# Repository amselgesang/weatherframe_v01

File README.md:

# weatherframe_v01
My weather station hardver

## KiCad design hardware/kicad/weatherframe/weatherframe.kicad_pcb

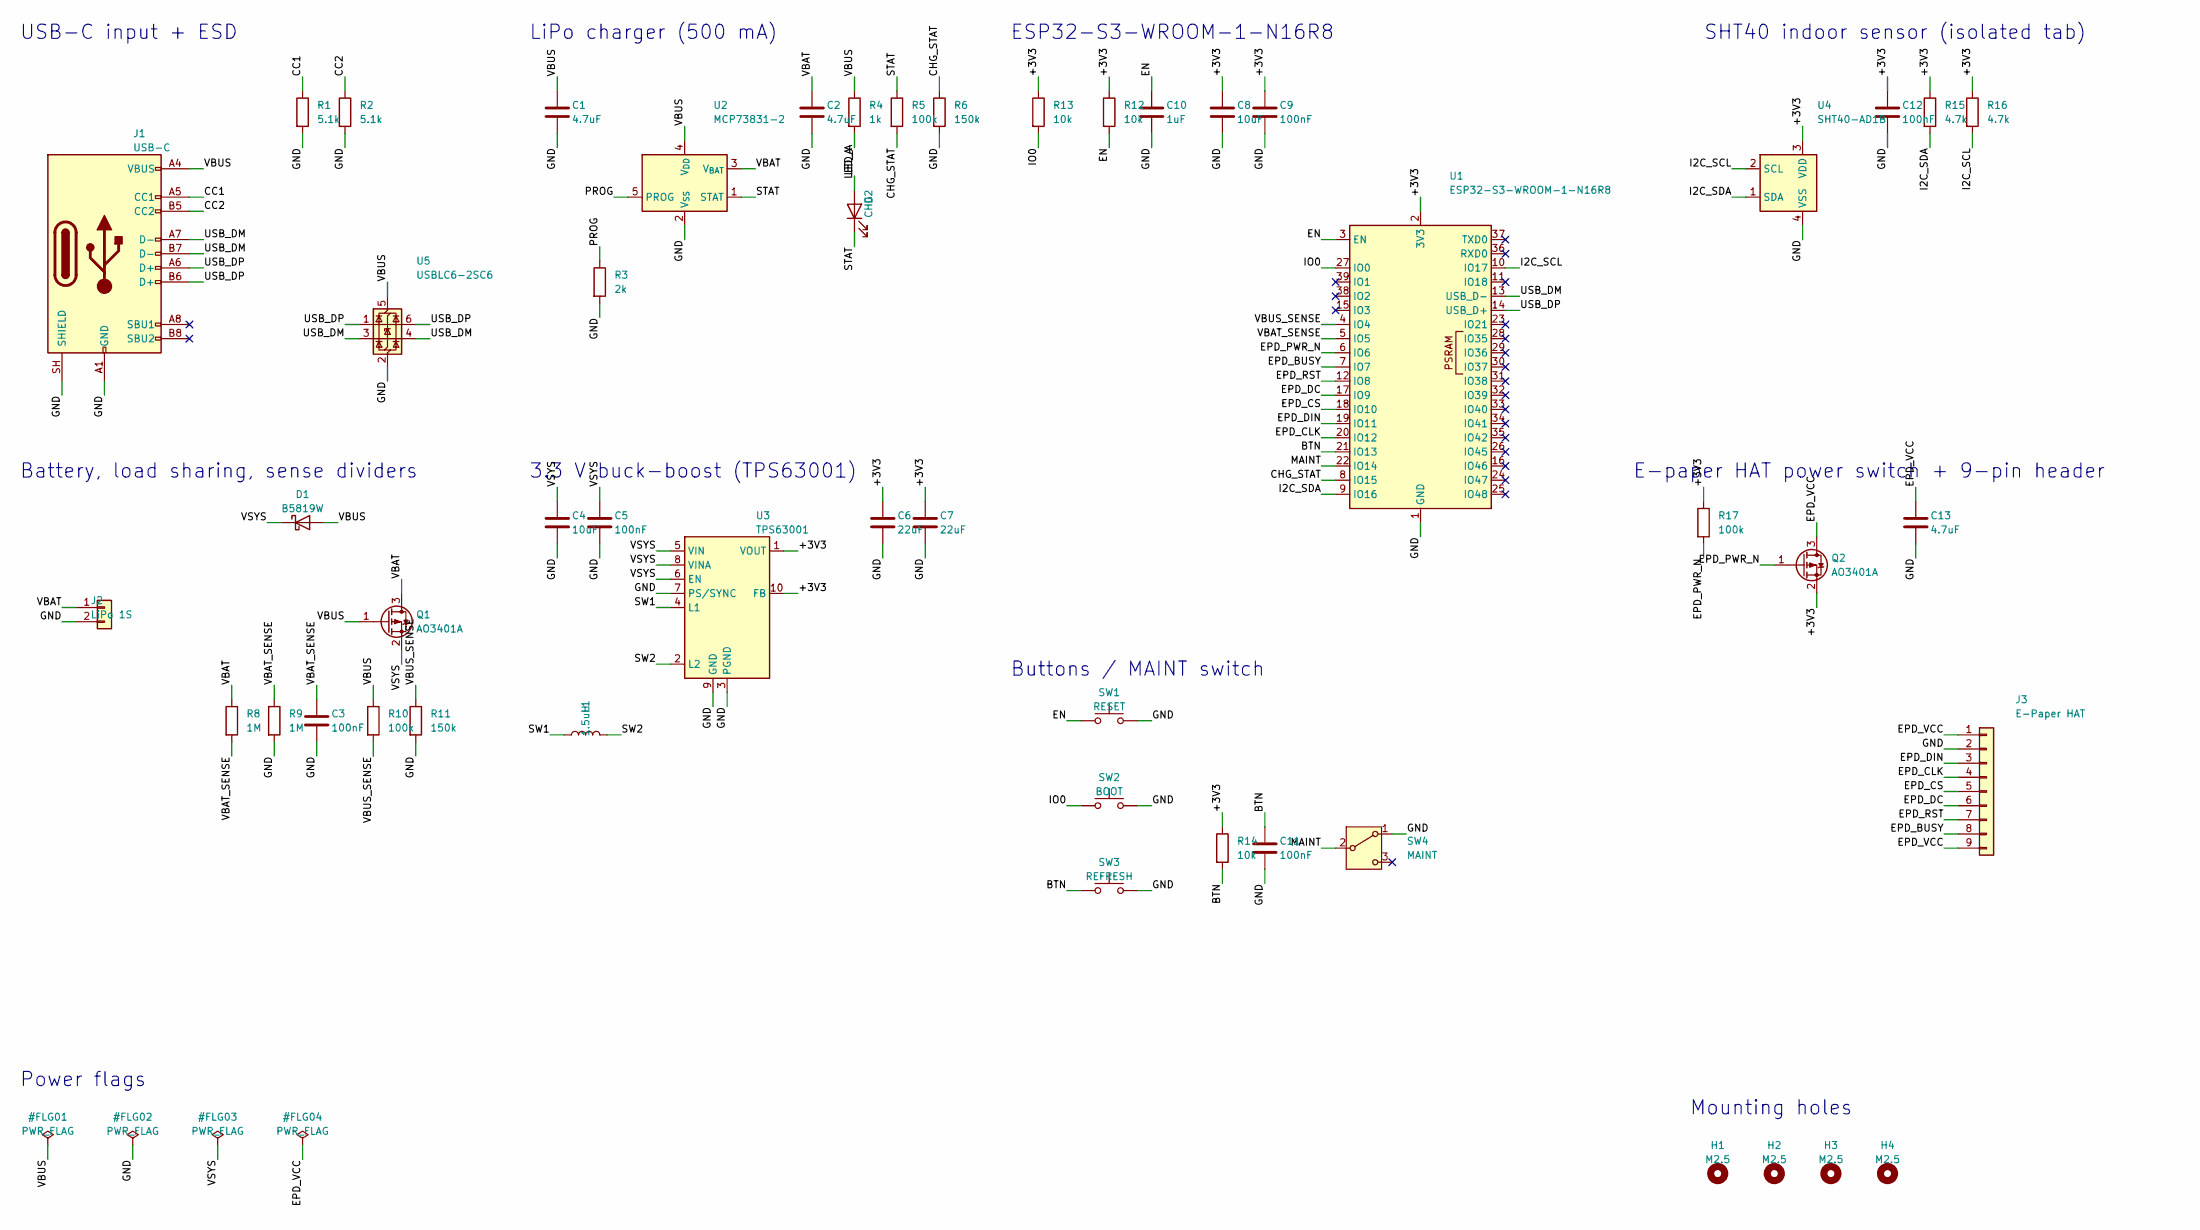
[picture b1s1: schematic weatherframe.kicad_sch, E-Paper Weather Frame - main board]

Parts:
C1, C2, C13: 4.7uF; C_0603_1608Metric; MPN 4.7uF; LCSC C19666
C3, C5, C9, C11, C12: 100nF; C_0402_1005Metric; MPN 100nF; LCSC C1525
C4: 10uF; C_0805_2012Metric; MPN 10uF; LCSC C15850
C6, C7: 22uF; C_0805_2012Metric; MPN 22uF; LCSC C45783
C8: 10uF; C_0603_1608Metric; MPN 10uF; LCSC C19702
C10: 1uF; C_0402_1005Metric; MPN 1uF; LCSC C52923
D1: B5819W; D_SOD-123; MPN B5819W; LCSC C8598
D2: CHG; LED_0603_1608Metric; MPN KT-0603R; LCSC C2286
H1, H2, H3, H4: M2.5; MountingHole_2.7mm_M2.5; MPN M2.5
J1: USB-C; USB_C_Receptacle_HRO_TYPE-C-31-M-12; MPN TYPE-C-31-M-12; LCSC C165948
J2: LiPo 1S; JST_PH_S2B-PH-SM4-TB_1x02-1MP_P2.00mm_Horizontal; MPN PH-2AWT (JST PH 2.0); LCSC C2763693
J3: E-Paper HAT; PinHeader_1x09_P2.54mm_Vertical; MPN 1x9 pin header 2.54 mm (hand-solder)
L1: 1.5uH; L_Changjiang_FNR4030S; MPN SWPA4030S1R5NT; LCSC C42100
Q1, Q2: AO3401A; SOT-23; MPN AO3401A; LCSC C15127
R1, R2: 5.1k; R_0402_1005Metric; MPN 5.1k; LCSC C25905
R3: 2k; R_0402_1005Metric; MPN 2k; LCSC C4109
R4: 1k; R_0402_1005Metric; MPN 1k; LCSC C11702
R5, R10, R17: 100k; R_0402_1005Metric; MPN 100k; LCSC C25741
R6, R11: 150k; R_0402_1005Metric; MPN 100k; LCSC C25755
R8, R9: 1M; R_0402_1005Metric; MPN 1M; LCSC C26083
R12, R13, R14: 10k; R_0402_1005Metric; MPN 10k; LCSC C25744
R15, R16: 4.7k; R_0402_1005Metric; MPN 4.7k; LCSC C25900
SW1: RESET; SW_Push_1P1T_XKB_TS-1187A; MPN TS-1187A-B-A-B; LCSC C318884
SW2: BOOT; SW_Push_1P1T_XKB_TS-1187A; MPN TS-1187A-B-A-B; LCSC C318884
SW3: REFRESH; SW_Push_1P1T_XKB_TS-1187A; MPN TS-1187A-B-A-B; LCSC C318884
SW4: MAINT; SW_SPDT_Shouhan_MSK12C02; MPN MSK12C02; LCSC C431540
U1: ESP32-S3-WROOM-1-N16R8; ESP32-S3-WROOM-1; MPN ESP32-S3-WROOM-1-N16R8; LCSC C2913202
U2: MCP73831-2; SOT-23-5; MPN MCP73831T-2ACI/OT; LCSC C424093
U3: TPS63001; Texas_DRC0010J; MPN TPS63001DRCR; LCSC C28060
U4: SHT40-AD1B; Sensirion_DFN-4_1.5x1.5mm_P0.8mm_SHT4x_NoCentralPad; MPN SHT40-AD1B-R2; LCSC C2909890
U5: USBLC6-2SC6; SOT-23-6; MPN USBLC6-2SC6; LCSC C7519

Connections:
+3V3: C6.1, C7.1, C8.1, C9.1, C12.1, Q2.2 (S), R12.1, R13.1, R14.1, R15.1, R16.1, R17.1, U1.2 (3V3), U3.1 (VOUT), U3.10 (FB), U4.3 (VDD)
BTN: C11.1, R14.2, SW3.1, U1.21 (IO13)
CC1: J1.A5 (CC1), R1.1
CC2: J1.B5 (CC2), R2.1
CHG_STAT: R5.2, R6.1, U1.8 (IO15)
EN: C10.1, R12.2, SW1.1, U1.3 (EN)
EPD_BUSY: J3.8, U1.7 (IO7)
EPD_CLK: J3.4, U1.20 (IO12)
EPD_CS: J3.5, U1.18 (IO10)
EPD_DC: J3.6, U1.17 (IO9)
EPD_DIN: J3.3, U1.19 (IO11)
EPD_PWR_N: Q2.1 (G), R17.2, U1.6 (IO6)
EPD_RST: J3.7, U1.12 (IO8)
EPD_VCC: C13.1, J3.1, J3.9, Q2.3 (D)
GND: C1.2, C2.2, C3.2, C4.2, C5.2, C6.2, C7.2, C8.2, C9.2, C10.2, C11.2, C12.2, C13.2, J1.A1 (GND), J1.A12 (GND), J1.B1 (GND), J1.B12 (GND), J1.SH (SHIELD), J2.2, J3.2, R1.2, R2.2, R3.2, R6.2, R9.2, R11.2, SW1.2, SW2.2, SW3.2, SW4.1 (A), SW4.SH, U1.1 (GND), U1.40 (GND), U1.41 (GND), U2.2 (V_{SS}), U3.3 (PGND), U3.7 (PS/SYNC), U3.9 (GND), U3.11 (PGND), U4.4 (VSS), U5.2 (GND)
I2C_SCL: R16.2, U1.10 (IO17), U4.2 (SCL)
I2C_SDA: R15.2, U1.9 (IO16), U4.1 (SDA)
IO0: R13.2, SW2.1, U1.27 (IO0)
LED_A: D2.2 (A), R4.2
MAINT: SW4.2 (B), U1.22 (IO14)
PROG: R3.1, U2.5 (PROG)
STAT: D2.1 (K), R5.1, U2.1 (STAT)
SW1: L1.1, U3.4 (L1)
SW2: L1.2, U3.2 (L2)
USB_DM: J1.A7 (D-), J1.B7 (D-), U1.13 (USB_D-), U5.3 (I/O2), U5.4 (I/O2)
USB_DP: J1.A6 (D+), J1.B6 (D+), U1.14 (USB_D+), U5.1 (I/O1), U5.6 (I/O1)
VBAT: C2.1, J2.1, Q1.3 (D), R8.1, U2.3 (V_{BAT})
VBAT_SENSE: C3.1, R8.2, R9.1, U1.5 (IO5)
VBUS: C1.1, D1.2 (A), J1.A4 (VBUS), J1.A9 (VBUS), J1.B4 (VBUS), J1.B9 (VBUS), Q1.1 (G), R4.1, R10.1, U2.4 (V_{DD}), U5.5 (VBUS)
VBUS_SENSE: R10.2, R11.1, U1.4 (IO4)
VSYS: C4.1, C5.1, D1.1 (K), Q1.2 (S), U3.5 (VIN), U3.6 (EN), U3.8 (VINA)

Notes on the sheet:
USB-C input + ESD
LiPo charger (500 mA)
Battery, load sharing, sense dividers
3.3 V buck-boost (TPS63001)
ESP32-S3-WROOM-1-N16R8
Buttons / MAINT switch
SHT40 indoor sensor (isolated tab)
E-paper HAT power switch + 9-pin header
Mounting holes
Power flags

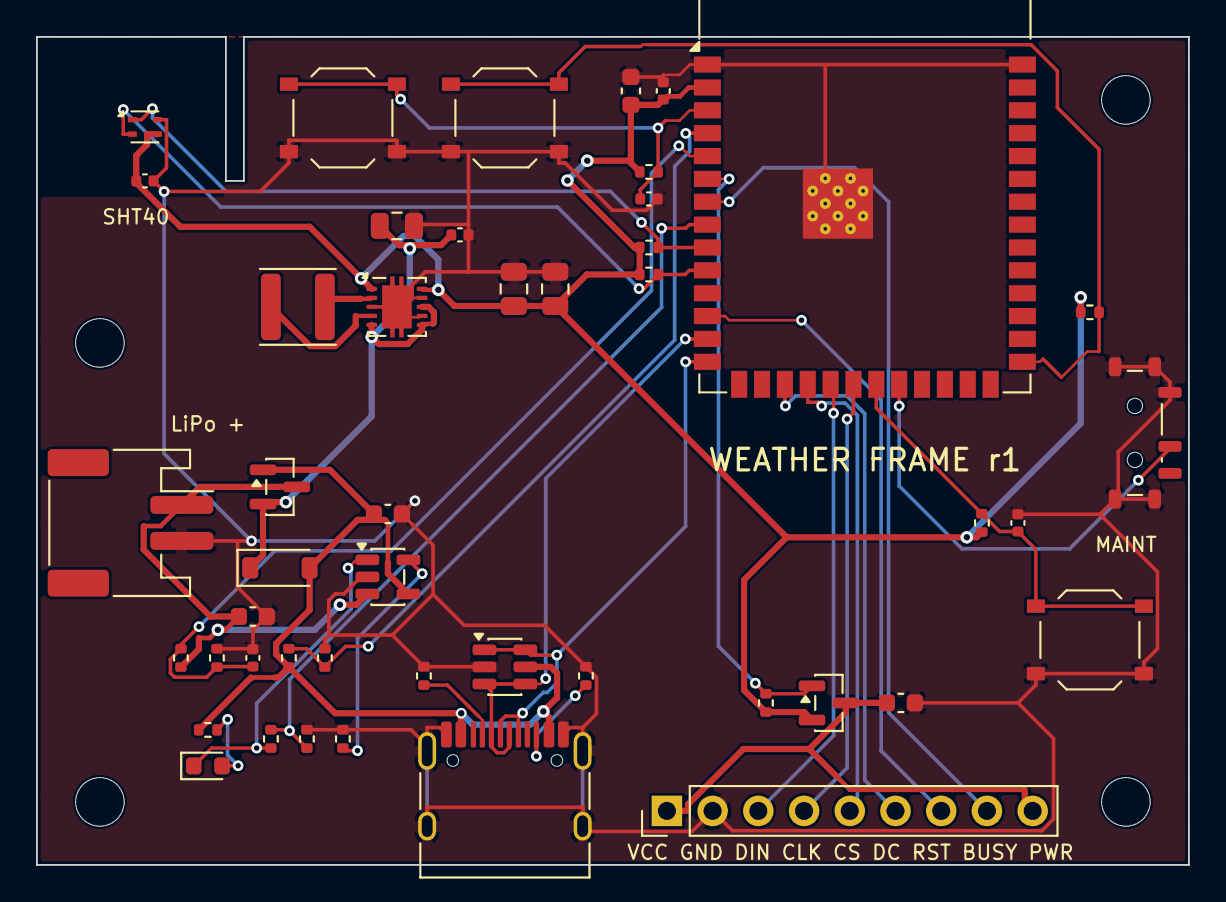
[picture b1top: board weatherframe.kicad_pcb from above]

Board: 2 copper layers, 64.0 x 46.0 mm, 50 parts (0 on the bottom side), 31 nets.

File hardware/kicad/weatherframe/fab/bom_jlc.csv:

Comment,Designator,Footprint,LCSC Part #
USB-C,J1,USB_C_Receptacle_HRO_TYPE-C-31-M-12,C165948
5.1k,"R1,R2",R_0402_1005Metric,C25905
USBLC6-2SC6,U5,SOT-23-6,C7519
MCP73831-2,U2,SOT-23-5,C424093
4.7uF,"C1,C2,C13",C_0603_1608Metric,C19666
2k,R3,R_0402_1005Metric,C4109
1k,R4,R_0402_1005Metric,C11702
CHG,D2,LED_0603_1608Metric,C2286
100k,"R5,R10,R17",R_0402_1005Metric,C25741
150k,"R6,R11",R_0402_1005Metric,C25755
LiPo 1S,J2,JST_PH_S2B-PH-SM4-TB_1x02-1MP_P2.00mm_Horizontal,C2763693
B5819W,D1,D_SOD-123,C8598
AO3401A,"Q1,Q2",SOT-23,C15127
1M,"R8,R9",R_0402_1005Metric,C26083
100nF,"C3,C5,C9,C11,C12",C_0402_1005Metric,C1525
TPS63001,U3,Texas_DRC0010J,C28060
1.5uH,L1,L_Changjiang_FNR4030S,C42100
10uF,C4,C_0805_2012Metric,C15850
22uF,"C6,C7",C_0805_2012Metric,C45783
ESP32-S3-WROOM-1-N16R8,U1,ESP32-S3-WROOM-1,C2913202
10uF,C8,C_0603_1608Metric,C19702
10k,"R12,R13,R14",R_0402_1005Metric,C25744
1uF,C10,C_0402_1005Metric,C52923
RESET,SW1,SW_Push_1P1T_XKB_TS-1187A,C318884
BOOT,SW2,SW_Push_1P1T_XKB_TS-1187A,C318884
REFRESH,SW3,SW_Push_1P1T_XKB_TS-1187A,C318884
MAINT,SW4,SW_SPDT_Shouhan_MSK12C02,C431540
SHT40-AD1B,U4,Sensirion_DFN-4_1.5x1.5mm_P0.8mm_SHT4x_NoCentralPad,C2909890
4.7k,"R15,R16",R_0402_1005Metric,C25900

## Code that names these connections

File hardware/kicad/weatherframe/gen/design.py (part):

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    R("R2", "5.1k", "CC2", "GND", (83.82, 50.8), pcb=(30.5, 35.5, 90, "F")),
    dict(ref="U5", sym="Power_Protection:USBLC6-2SC6", fp="Package_TO_SOT_SMD:SOT-23-6",
         value="USBLC6-2SC6", lcsc="C7519", mpn="USBLC6-2SC6",
         pins={"1": "USB_DP", "6": "USB_DP", "3": "USB_DM", "4": "USB_DM", "2": "GND", "5": "VBUS"},
         pos=(91.44, 88.9), pcb=(26, 35.0, 0, "F")),

    # ---------------- Charger ----------------
    dict(ref="U2", sym="Battery_Management:MCP73831-2-OT", fp="Package_TO_SOT_SMD:SOT-23-5",
         value="MCP73831-2", lcsc="C424093", mpn="MCP73831T-2ACI/OT",
         pins={"4": "VBUS", "2": "GND", "3": "VBAT", "5": "PROG", "1": "STAT"},
         pos=(144.78, 63.5), pcb=(19.5, 30, 0, "F")),
    C("C1", "4.7uF", "VBUS", "GND", (121.92, 50.8), fp=C0603, pcb=(19.5, 26.5, 0, "F")),
    C("C2", "4.7uF", "VBAT", "GND", (167.64, 50.8), fp=C0603, pcb=(12, 32.2, 0, "F")),
    R("R3", "2k", "PROG", "GND", (129.54, 81.28), pcb=(17, 39, 90, "F")),           # 500 mA charge current
    R("R4", "1k", "VBUS", "LED_A", (175.26, 50.8), pcb=(9.5, 38.5, 0, "F")),
    dict(ref="D2", sym="Device:LED", fp="LED_SMD:LED_0603_1608Metric", value="CHG", lcsc="C2286", mpn="KT-0603R",
         pins={"2": "LED_A", "1": "STAT"}, pos=(175.26, 68.58), rot=90, pcb=(9.5, 40.5, 0, "F")),
    R("R5", "100k", "STAT", "CHG_STAT", (182.88, 50.8), pcb=(13, 39, 90, "F")),
    R("R6", "150k", "CHG_STAT", "GND", (190.5, 50.8), pcb=(15, 39, 90, "F")),      # 100k/150k: 5 V -> 3.0 V (ESP32-S3 VIH min = 2.475 V)

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         value="LiPo 1S", lcsc="C2763693", mpn="PH-2AWT (JST PH 2.0)",
         pins={"1": "VBAT", "2": "GND"}, pos=(40.64, 139.7), pcb=(5.2, 27, -90, "F")),
    dict(ref="D1", sym="Device:D_Schottky", fp="Diode_SMD:D_SOD-123", value="B5819W", lcsc="C8598", mpn="B5819W",
         pins={"2": "VBUS", "1": "VSYS"}, pos=(76.2, 124.46), pcb=(13.5, 29.5, 0, "F")),
    dict(ref="Q1", sym="Transistor_FET:AO3401A", fp="Package_TO_SOT_SMD:SOT-23", value="AO3401A", lcsc="C15127", mpn="AO3401A",
         pins={"1": "VBUS", "2": "VSYS", "3": "VBAT"}, pos=(91.44, 142.24), pcb=(13.5, 25, 0, "F")),
    R("R8", "1M", "VBAT", "VBAT_SENSE", (63.5, 160.02), pcb=(8, 34.5, 90, "F")),
    R("R9", "1M", "VBAT_SENSE", "GND", (71.12, 160.02), pcb=(10, 34.5, 90, "F")),
    C("C3", "100nF", "VBAT_SENSE", "GND", (78.74, 160.02), pcb=(12, 34.5, 90, "F")),
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    # ---------------- 3.3 V buck-boost ----------------
    dict(ref="U3", sym="Regulator_Switching:TPS63001", fp="Package_SON:Texas_DRC0010J",
         value="TPS63001", lcsc="C28060", mpn="TPS63001DRCR",
         pins={"5": "VSYS", "8": "VSYS", "6": "VSYS", "7": "GND", "3": "GND", "11": "GND", "9": "GND",
               "4": "SW1", "2": "SW2", "1": "+3V3", "10": "+3V3"},
         pos=(152.4, 139.7), pcb=(20, 15, 0, "F")),
    dict(ref="L1", sym="Device:L", fp="Inductor_SMD:L_Changjiang_FNR4030S", value="1.5uH", lcsc="C42100",
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    dict(ref="SW2", sym="Switch:SW_Push", fp="Button_Switch_SMD:SW_Push_1P1T_XKB_TS-1187A", value="BOOT",
         lcsc="C318884", mpn="TS-1187A-B-A-B", pins={"1": "IO0", "2": "GND"}, pos=(220.98, 175.26), pcb=(26, 4.5, 0, "F")),
    dict(ref="SW3", sym="Switch:SW_Push", fp="Button_Switch_SMD:SW_Push_1P1T_XKB_TS-1187A", value="REFRESH",
         lcsc="C318884", mpn="TS-1187A-B-A-B", pins={"1": "BTN", "2": "GND"}, pos=(220.98, 190.5), pcb=(58.5, 33.5, 0, "F")),
    R("R14", "10k", "+3V3", "BTN", (241.3, 182.88), pcb=(52.5, 27, 90, "F")),
    C("C11", "100nF", "BTN", "GND", (248.92, 182.88), pcb=(54.5, 27, 90, "F")),
    dict(ref="SW4", sym="Switch:SW_SPDT", fp="Button_Switch_SMD:SW_SPDT_Shouhan_MSK12C02", value="MAINT",
         lcsc="C431540", mpn="MSK12C02", pins={"2": "MAINT", "1": "GND", "3": None}, pos=(266.7, 182.88),
         pcb=(61.0, 22, -90, "F")),

    # ---------------- SHT40 (on the isolated corner tab) ----------------
    dict(ref="U4", sym="Sensor_Humidity:SHT4x", fp="Sensor_Humidity:Sensirion_DFN-4_1.5x1.5mm_P0.8mm_SHT4x_NoCentralPad",
         value="SHT40-AD1B", lcsc="C2909890", mpn="SHT40-AD1B-R2",
         pins={"1": "I2C_SDA", "2": "I2C_SCL", "3": "+3V3", "4": "GND"}, pos=(342.9, 63.5), pcb=(6, 5, 0, "F")),
    C("C12", "100nF", "+3V3", "GND", (360.68, 50.8), pcb=(6, 8, 0, "F")),
    R("R15", "4.7k", "+3V3", "I2C_SDA", (368.3, 50.8), pcb=(34, 11.7, 0, "F")),
    R("R16", "4.7k", "+3V3", "I2C_SCL", (375.92, 50.8), pcb=(34, 13.2, 0, "F")),

    # ---------------- E-paper power switch + header ----------------
    dict(ref="Q2", sym="Transistor_FET:AO3401A", fp="Package_TO_SOT_SMD:SOT-23", value="AO3401A", lcsc="C15127", mpn="AO3401A",
         pins={"1": "EPD_PWR_N", "2": "+3V3", "3": "EPD_VCC"}, pos=(345.44, 132.08), pcb=(44, 37, 0, "F")),
    R("R17", "100k", "+3V3", "EPD_PWR_N", (327.66, 124.46), pcb=(40.5, 37, 90, "F")),
    C("C13", "4.7uF", "EPD_VCC", "GND", (365.76, 124.46), fp=C0603, pcb=(48, 37, 0, "F")),
    dict(ref="J3", sym="Connector_Generic:Conn_01x09", fp="Connector_PinHeader_2.54mm:PinHeader_1x09_P2.54mm_Vertical",
         value="E-Paper HAT", lcsc="", mpn="1x9 pin header 2.54 mm (hand-solder)",
         pins={"1": "EPD_VCC", "2": "GND", "3": "EPD_DIN", "4": "EPD_CLK", "5": "EPD_CS", "6": "EPD_DC",
               "7": "EPD_RST", "8": "EPD_BUSY", "9": "EPD_VCC"},
         pos=(378.46, 172.72), pcb=(35, 43, 90, "F"), hand_solder=True),

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
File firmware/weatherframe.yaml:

# E-paper weather frame — device firmware for the custom ESP32-S3 board.
#   esphome run weatherframe.yaml          (first time over USB-C, later OTA in MAINT mode)
#
# Wake cycle (every 15 min, aligned to :00/:15/:30/:45):
#   boot -> read SHT40 + battery -> Wi-Fi -> Open-Meteo -> refresh e-paper -> deep sleep
# MAINT switch ON keeps the board awake for OTA and logs. The button forces a refresh.

substitutions:
  name: weatherframe
  location_name: "Budapest"
  latitude: "47.4979"
  longitude: "19.0402"
  german: "true"          # "false" for English labels
  fahrenheit: "false"     # "true" for °F / mph
  interval_s: "900"       # wake interval in seconds
  quiet_start: "0"        # no updates from 00:00 ...
  quiet_end: "6"          # ... until 06:00 local time (set both equal to disable)
  low_battery_v: "3.40"

  # Pin map (must match hardware/kicad/weatherframe)
  pin_sda: GPIO16
  pin_scl: GPIO17
  pin_vbus: GPIO4
  pin_vbat: GPIO5
  pin_epd_pwr: GPIO6      # low = HAT powered (P-FET gate)
  pin_epd_busy: GPIO7
  pin_epd_rst: GPIO8
  pin_epd_dc: GPIO9
  pin_epd_cs: GPIO10
  pin_epd_mosi: GPIO11
  pin_epd_clk: GPIO12
  pin_button: GPIO13
  pin_maint: GPIO14
  pin_chg: GPIO15

esphome:
  name: ${name}
  friendly_name: Weather Frame
  on_boot:
    priority: -100
    then:
      - script.execute: wake_cycle

esp32:
  variant: esp32s3
  board: esp32-s3-devkitc-1
  flash_size: 16MB
  framework:
    type: esp-idf

psram:
  mode: octal
  speed: 80MHz

packages:
  common: !include weatherframe/common.yaml

logger:
  level: INFO
  hardware_uart: USB_SERIAL_JTAG

wifi:
  ssid: !secret wifi_ssid
  password: !secret wifi_password
  fast_connect: true
  reboot_timeout: 0s
  power_save_mode: light
  # A static IP saves ~1 s of DHCP per wake. Uncomment and adjust:
  # manual_ip:
  #   static_ip: 192.168.1.60
  #   gateway: 192.168.1.1
  #   subnet: 255.255.255.0
  #   dns1: 192.168.1.1

ota:
  - platform: esphome
    password: !secret ota_password

time:
  - platform: sntp
    id: wf_clock

deep_sleep:
  id: sleeper
  sleep_duration: 15min
  run_duration: 90s       # safety net: never stay awake longer than this (unless MAINT)
  wakeup_pin:
    number: ${pin_button}
    inverted: true        # button pulls low; external 10k pull-up on the board
    allow_other_uses: true

i2c:
  sda: ${pin_sda}
  scl: ${pin_scl}
  frequency: 400kHz

spi:
  clk_pin: ${pin_epd_clk}
  mosi_pin: ${pin_epd_mosi}

sensor:
  - platform: sht4x
    id: sht40
    update_interval: never
    precision: High
    heater_max_duty: 0
    temperature:
      id: indoor_temp
      name: Indoor temperature
    humidity:
      id: indoor_hum
      name: Indoor humidity

  - platform: adc
    id: vbat
    name: Battery voltage
    pin: ${pin_vbat}
    attenuation: 12db
    samples: 16
    update_interval: never
    filters:
      - multiply: 2.0     # 1M/1M divider

binary_sensor:
  - platform: gpio
    id: usb_power
    name: USB power
    pin: ${pin_vbus}      # VBUS via 100k/150k divider (5 V -> 3.0 V)
  - platform: gpio
    id: chg_stat
    pin: ${pin_chg}       # MCP73831 STAT via 100k/150k divider: low = charging, high = done
  - platform: template
    id: charging
    name: Charging
    lambda: return id(usb_power).state && !id(chg_stat).state;
  - platform: gpio
    id: maint
    name: Maintenance switch
    pin:
      number: ${pin_maint}
      inverted: true      # switch to GND = maintenance
      mode:
        input: true
        pullup: true
    on_press:
      - deep_sleep.prevent: sleeper
    on_release:
      - deep_sleep.allow: sleeper
  - platform: gpio
    id: button
    name: Refresh button
    pin:
      number: ${pin_button}
      inverted: true
      allow_other_uses: true
    on_press:
      - script.execute: wake_cycle

display:
  - platform: epaper_spi
    id: epd
    model: waveshare-7.5in-v2
    cs_pin: ${pin_epd_cs}
    dc_pin: ${pin_epd_dc}
    reset_pin: ${pin_epd_rst}
    busy_pin:
      number: ${pin_epd_busy}
      inverted: true      # UC8179 BUSY is low while busy
    enable_pin:
      number: ${pin_epd_pwr}
      inverted: true      # drives the P-FET gate low = HAT on
    update_interval: never
    lambda: ${render_lambda}

script:
  - id: wake_cycle
    mode: single
    then:
      - if:
          condition:
            binary_sensor.is_on: maint
          then:
            - deep_sleep.prevent: sleeper
      # Read the room before Wi-Fi and the regulator warm the board up.
      - component.update: sht40
      - component.update: vbat
      - lambda: |-
          id(low_battery) = id(vbat).has_state() && id(vbat).state < ${low_battery_v} && !id(usb_power).state;
      - if:
          condition:
            lambda: return !id(low_battery);
          then:
            - wait_until:
                condition:
                  wifi.connected:
                timeout: 15s
            - if:
                condition:
                  wifi.connected:
                then:
                  - wait_until:
                      condition:
                        lambda: return id(wf_clock).now().is_valid();
                      timeout: 3s
                  - script.execute: fetch_weather
                  - script.wait: fetch_weather
      - component.update: epd
      - delay: 200ms
      - wait_until:
          condition:
            lambda: return id(epd).is_idle();
          timeout: 30s
      - if:
          condition:
            binary_sensor.is_off: maint
          then:
            - deep_sleep.enter:
                id: sleeper
                # Low battery: only wake for the button or to re-check every 6 h.
                sleep_duration: !lambda |-
                  if (id(low_battery)) return 6u * 3600u * 1000u;
                  auto now = id(wf_clock).now();
                  return wf::next_sleep_ms(now.is_valid() ? now.timestamp : 0,
                                           ${interval_s}, ${quiet_start}, ${quiet_end});
